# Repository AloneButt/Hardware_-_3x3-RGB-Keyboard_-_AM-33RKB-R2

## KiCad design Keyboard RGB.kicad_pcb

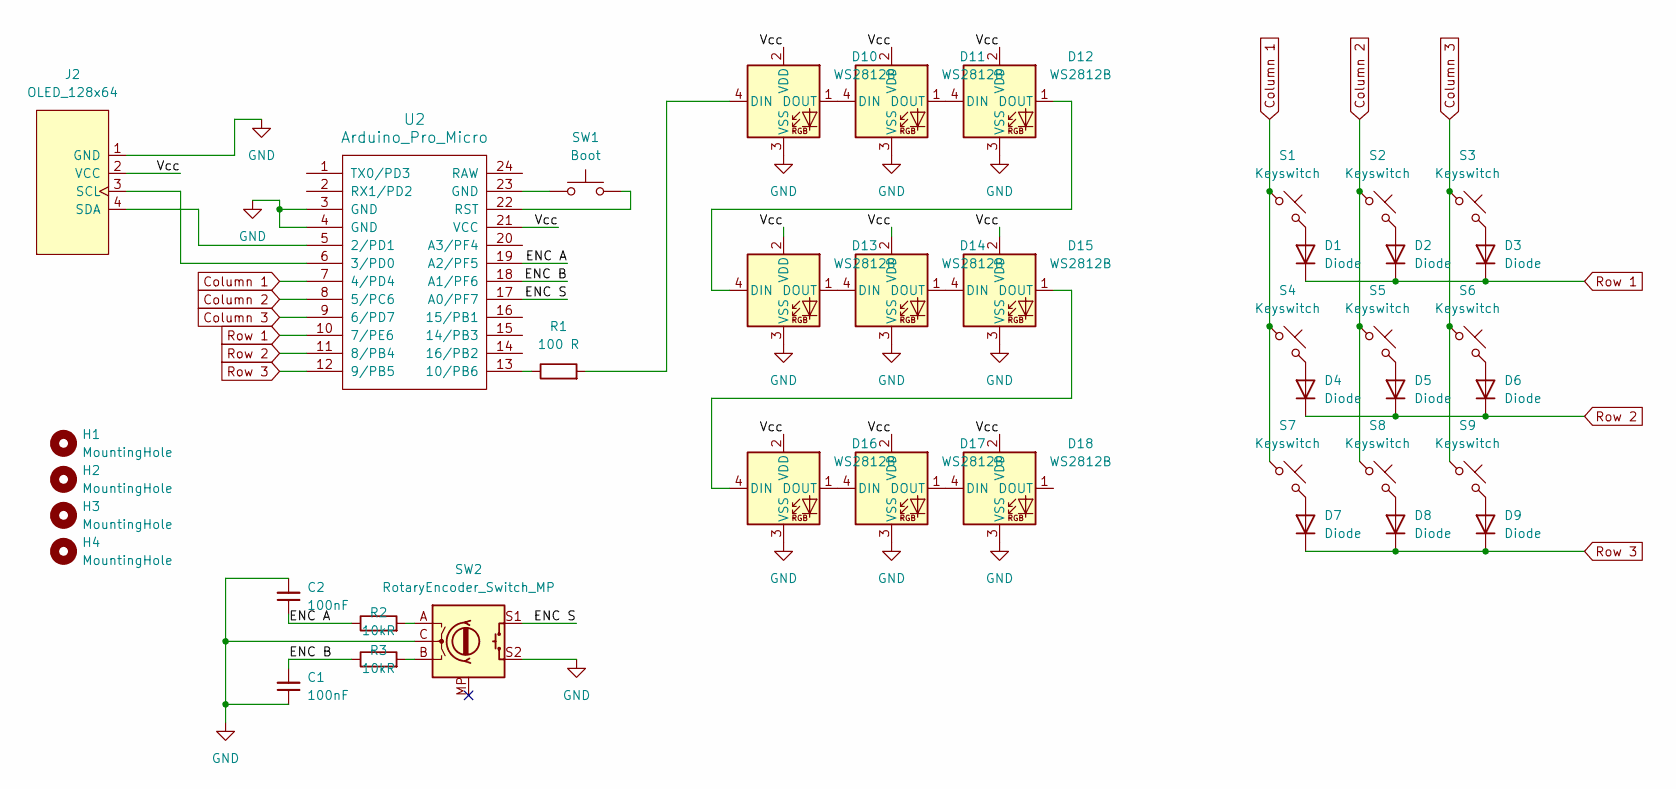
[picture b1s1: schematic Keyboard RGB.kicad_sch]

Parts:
C1, C2: 100nF; C_0805_2012Metric_Pad1.18x1.45mm_HandSolder
D1, D2, D3, D4, D5, D6, D7, D8, D9: Diode; Diode_SOD-123
D10, D11, D12, D13, D14, D15, D16, D17, D18: WS2812B; Soso_RGB LED 1.6x1.5mm
H1, H2, H3, H4: MountingHole; MountingHole_3.2mm_M3_DIN965_Pad
J2: OLED_128x64; JST_EH_B4B-EH-A_1x04_P2.50mm_Vertical
R1: 100 R; R_0805_2012Metric_Pad1.20x1.40mm_HandSolder
R2, R3: 10kR; R_0805_2012Metric_Pad1.20x1.40mm_HandSolder
S1, S2, S3, S4, S5, S6, S7, S8, S9: Keyswitch; MX_PCB_1.00u
SW1: Boot; SW_PUSH_6mm_H4.3mm
SW2: RotaryEncoder_Switch_MP; RotaryEncoder_Alps_EC11E-Switch_Vertical_H20mm
U2: Arduino_Pro_Micro

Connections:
/ENC A: C2.1, R2.1, U2.19 (A2/PF5)
/ENC B: C1.2, R3.1, U2.18 (A1/PF6)
/ENC S: SW2.S1, U2.17 (A0/PF7)
/Vcc: D10.2 (VDD), D11.2 (VDD), D12.2 (VDD), D13.2 (VDD), D14.2 (VDD), D15.2 (VDD), D16.2 (VDD), D17.2 (VDD), D18.2 (VDD), J2.2 (VCC), U2.21 (VCC)
Column 1: S1.1, S4.1, S7.1, U2.7 (4/PD4)
Column 2: S2.1, S5.1, S8.1, U2.8 (5/PC6)
Column 3: S3.1, S6.1, S9.1, U2.9 (6/PD7)
GND: C1.1, C2.2, D10.3 (VSS), D11.3 (VSS), D12.3 (VSS), D13.3 (VSS), D14.3 (VSS), D15.3 (VSS), D16.3 (VSS), D17.3 (VSS), D18.3 (VSS), J2.1 (GND), SW2.C, SW2.S2, U2.3 (GND), U2.4 (GND)
unnamed: D1.2 (A), S1.2
unnamed: D2.2 (A), S2.2
unnamed: D3.2 (A), S3.2
unnamed: D4.2 (A), S4.2
unnamed: D5.2 (A), S5.2
unnamed: D6.2 (A), S6.2
unnamed: D7.2 (A), S7.2
unnamed: D8.2 (A), S8.2
unnamed: D9.2 (A), S9.2
unnamed: D10.4 (DIN), R1.2
unnamed: D10.1 (DOUT), D11.4 (DIN)
unnamed: D11.1 (DOUT), D12.4 (DIN)
unnamed: D12.1 (DOUT), D13.4 (DIN)
unnamed: D13.1 (DOUT), D14.4 (DIN)
unnamed: D14.1 (DOUT), D15.4 (DIN)
unnamed: D15.1 (DOUT), D16.4 (DIN)
unnamed: D16.1 (DOUT), D17.4 (DIN)
unnamed: D17.1 (DOUT), D18.4 (DIN)
unnamed: J2.3 (SCL), U2.6 (3/PD0)
unnamed: J2.4 (SDA), U2.5 (2/PD1)
unnamed: R2.2, SW2.A
unnamed: R3.2, SW2.B
unnamed: SW1.1, U2.23 (GND)
unnamed: R1.1, U2.13 (10/PB6)
unnamed: SW1.2, U2.22 (RST)
Row 1: D1.1 (K), D2.1 (K), D3.1 (K), U2.10 (7/PE6)
Row 2: D4.1 (K), D5.1 (K), D6.1 (K), U2.11 (8/PB4)
Row 3: D7.1 (K), D8.1 (K), D9.1 (K), U2.12 (9/PB5)

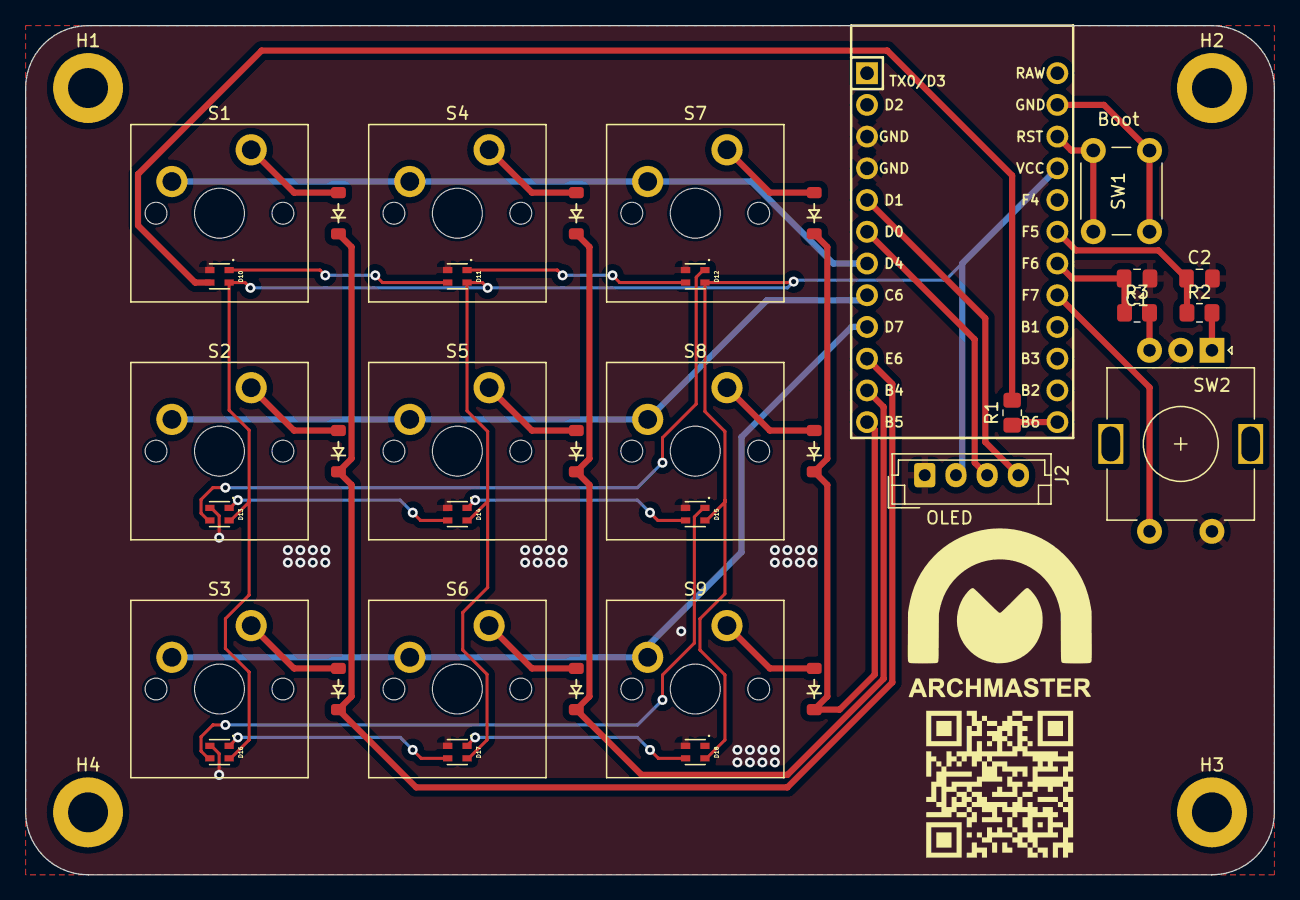
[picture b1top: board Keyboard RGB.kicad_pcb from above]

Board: 2 copper layers, 100.0 x 68.0 mm, 40 parts (0 on the bottom side), 36 nets.

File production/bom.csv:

Designator,Footprint,Quantity,Value,LCSC Part #
"C1, C2",0805,2,100nF,
"D1, D2, D3, D4, D5, D6, D7, D8, D9",Diode_SOD-123,9,Diode,
"D10, D11, D12, D13, D14, D15, D16, D17, D18",Soso_RGB LED 1.6x1.5mm,9,WS2812B,
J2,JST_EH_B4B-EH-A_1x04_P2.50mm_Vertical,1,OLED_128x64,
R1,0805,1,100 R,
"R2, R3",0805,2,10kR,
"S1, S2, S3, S4, S5, S6, S7, S8, S9",MX_PCB_1.00u,9,Keyswitch,
SW1,SW_PUSH_6mm_H4.3mm,1,Boot,
SW2,RotaryEncoder_Alps_EC11E-Switch_Vertical_H20mm,1,RotaryEncoder_Switch_MP,
U2,Arduino_Pro_Micro,1,Arduino_Pro_Micro,

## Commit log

2025-10-26 updated schematic
2025-10-26 cleaned schematic, updated traces, components and zones
2025-10-26 added EC11 encoder
2025-10-26 updated silkscreen

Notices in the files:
Keyboard RGB.kicad_pcb:
© 2025 ARCHMASTER. All Rights Reserved.
